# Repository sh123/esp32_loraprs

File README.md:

# ESP32 LoRa APRS Modem 

This project is amateur radio ESP32 based LoRa/FSK **KISS Bluetooth/BLE/USB/TCPIP** modem + LoRa **APRS-IS RX/TX iGate** server over WiFI + LoRa/FSK **APRS digipeater** + **Codec2 DV modem** (with Codec2 Talkie Android application). 

&#x26A0; **To configure sketch modify default parameters in config.h file or board specific pinouts in variants/[board]/variant.h.**

- For project description, detailed setup and more information, please, visit our Wiki at https://github.com/sh123/esp32_loraprs/wiki
- For discussions, visit https://github.com/sh123/esp32_loraprs/discussions

&#x26A0; Project also supports **APRSDroid TNC2 text APRS packet mode** (configurable), which makes it interoperable with other LoRa APRS trackers without AX25 support.

Supported module types: **SX126X**, **SX127X** and other modules supported by RadioLib, idle RX power consumption is around 60mA, so single 18650 cell should last for about 24 hours in RX.

Modules, which are used by users and known to work
- **SX126X** (**suggested**, 1W/2W modules will provide decent coverage for APRS, stable frequency suitable for < 125 kHz BW at 433 MHz, 5V from USB power bank is enough to power it, has additional LNA)
  - &#128077; **E22-400M30S/E22-400M33S (SX1268)**
  - E220-400M30S (LLCC68) BW125 SF from 7 to 9 (chip limitations)
  - These modules are 30dbm modules, but maximum power should be set to no more than 20-22dbm, see https://github.com/jgromes/RadioLib/wiki/High-power-Radio-Modules-Guide
- **SX127X** (low power, 50-100mW, temperature frequency drift, problematic for narrow band)
  - RA-01 (SX1278)
  - RA-02 (SX1276)
  - TTGO T-Beam (SX1276)

# Building
- Update `include/config.h` with your radio settings
  - If you are using lora-aprs iGate (non AX.25) then set `CFG_TEXT_PACKETS` and `CFG_TEXT_PACKETS_3` config parameters to `true` and use APRSDroid TNC2 connection protocol
- To build for client/tracker mode use `pio run -e esp32dev_e22_modem`
- To build for iGate mode use `pio run -e esp32dev_e22_igate`

# Development board
Development board schematics, case and antenna models are available under `extras/cad` and `extras/schematics`. 

Supported ESP32-DEV boards are with 36 and 38 pinouts (configured with solder pads) and ESP32-C3-MINI with separate dev board.

&#x26A0; **There are ESP32 boards with different socket widths: 22mm and 25mm, board files for 25mm have _wide suffix in file names.**

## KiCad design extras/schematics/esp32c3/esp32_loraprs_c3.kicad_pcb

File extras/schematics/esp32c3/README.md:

# ESP32-C3-MINI LoRa modem devboard

This is power bank style LoRA APRS modem based on ESP32-C3-DEV board with built in charge/boost IP5306 controller and battery holder on the back side.

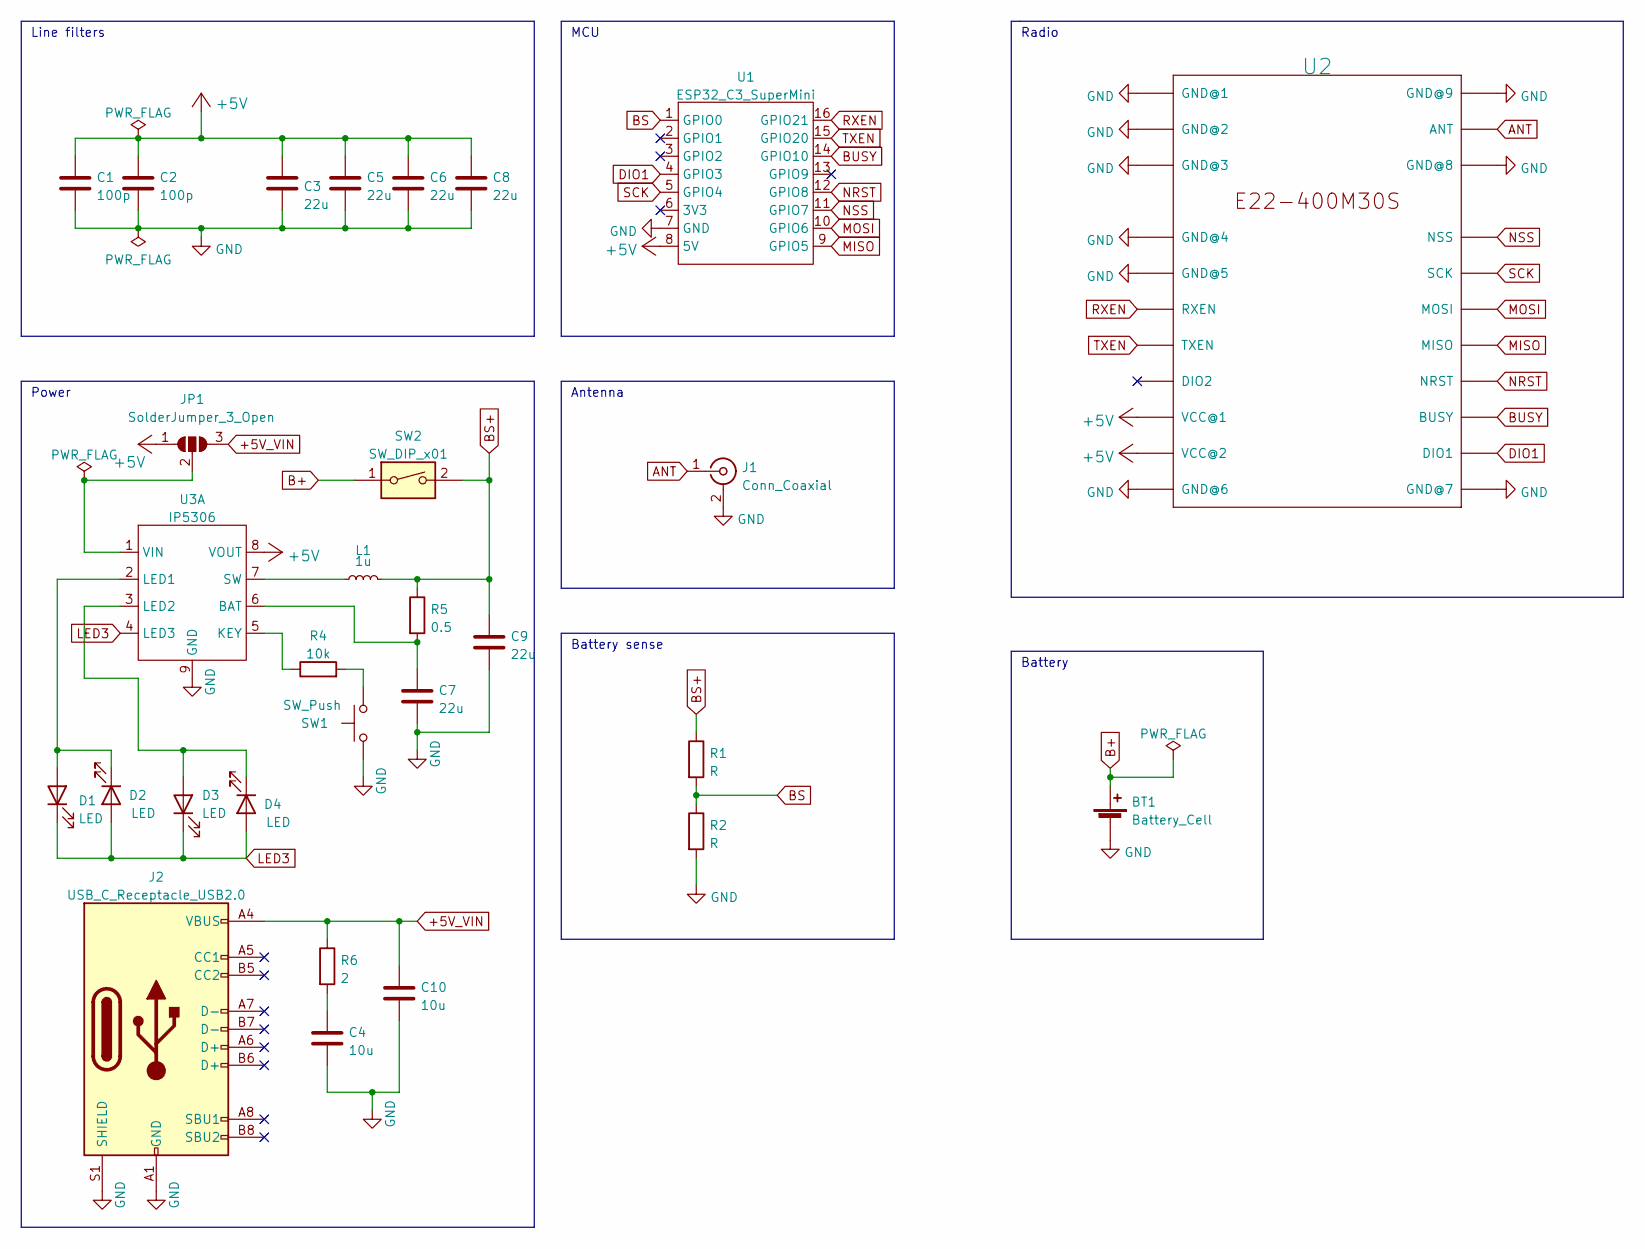
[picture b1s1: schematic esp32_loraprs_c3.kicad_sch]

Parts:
BT1: Battery_Cell; BatteryHolder_1x18650
C1, C2: 100p; C_0603_1608Metric_Pad1.08x0.95mm_HandSolder
C3, C5, C6, C7, C8, C9: 22u; C_0805_2012Metric_Pad1.18x1.45mm_HandSolder
C4, C10: 10u; C_0805_2012Metric_Pad1.18x1.45mm_HandSolder
D1, D2, D3, D4: LED; LED_0603_1608Metric_Pad1.05x0.95mm_HandSolder
J1: Conn_Coaxial; SMA_Samtec_SMA-J-P-X-ST-EM1_EdgeMount
J2: USB_C_Receptacle_USB2.0; USB_C_Receptacle_G-Switch_GT-USB-7010ASV
JP1: SolderJumper_3_Open; SolderJumper-3_P1.3mm_Open_RoundedPad1.0x1.5mm_NumberLabels
L1: 1u; L_6.3x6.3_H3
R1, R2: R; R_0603_1608Metric_Pad0.98x0.95mm_HandSolder
R4: 10k; R_0603_1608Metric_Pad0.98x0.95mm_HandSolder
R5: 0.5; R_0603_1608Metric_Pad0.98x0.95mm_HandSolder
R6: 2; R_0603_1608Metric_Pad0.98x0.95mm_HandSolder
SW1: SW_Push; Panasonic_EVQPUJ_EVQPUA
SW2: SW_DIP_x01; SW_SPST_REED_CT05-XXXX-J1
U1: ESP32_C3_SuperMini; esp32 c3 SuperMini
U2: E22-400M30S
U3: IP5306; HSOP-8-1EP_3.9x4.9mm_P1.27mm_EP2.3x2.3mm

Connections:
+5V: C1.1, C2.1, C3.1, C5.1, C6.1, C8.1, JP1.1 (A), U1.8 (5V), U2.9 (VCC@1), U2.10 (VCC@2), U3.8 (VOUT)
+5V_VIN: C10.1, J2.A4 (VBUS), J2.A9 (VBUS), J2.B4 (VBUS), J2.B9 (VBUS), JP1.3 (B), R6.1
ANT: J1.1 (In), U2.21 (ANT)
B+: BT1.1 (+), SW2.1
BS: R1.2, R2.1, U1.1 (GPIO0)
BS+: C9.1, L1.2, R1.1, R5.1, SW2.2
BUSY: U1.14 (GPIO10), U2.14 (BUSY)
DIO1: U1.4 (GPIO3), U2.13 (DIO1)
GND: BT1.2 (-), C1.2, C2.2, C3.2, C4.2, C5.2, C6.2, C7.2, C8.2, C9.2, C10.2, J1.2 (Ext), J2.A1 (GND), J2.A12 (GND), J2.B1 (GND), J2.B12 (GND), J2.S1 (SHIELD), R2.2, SW1.1, U1.7 (GND), U2.1 (GND@1), U2.2 (GND@2), U2.3 (GND@3), U2.4 (GND@4), U2.5 (GND@5), U2.11 (GND@6), U2.12 (GND@7), U2.20 (GND@8), U2.22 (GND@9), U3.9 (GND)
LED3: D1.1 (K), D2.2 (A), D3.1 (K), D4.2 (A), U3.4 (LED3)
MISO: U1.9 (GPIO5), U2.16 (MISO)
MOSI: U1.10 (GPIO6), U2.17 (MOSI)
NRST: U1.12 (GPIO8), U2.15 (NRST)
NSS: U1.11 (GPIO7), U2.19 (NSS)
unnamed: C4.1, R6.2
unnamed: C7.1, R5.2, U3.6 (BAT)
unnamed: D1.2 (A), D2.1 (K), U3.2 (LED1)
unnamed: D3.2 (A), D4.1 (K), U3.3 (LED2)
unnamed: JP1.2 (C), U3.1 (VIN)
unnamed: L1.1, U3.7 (SW)
unnamed: R4.1, U3.5 (KEY)
unnamed: R4.2, SW1.2
RXEN: U1.16 (GPIO21), U2.6 (RXEN)
SCK: U1.5 (GPIO4), U2.18 (SCK)
TXEN: U1.15 (GPIO20), U2.7 (TXEN)

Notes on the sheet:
Radio
MCU
Line filters
Battery sense
Power
Battery
Antenna

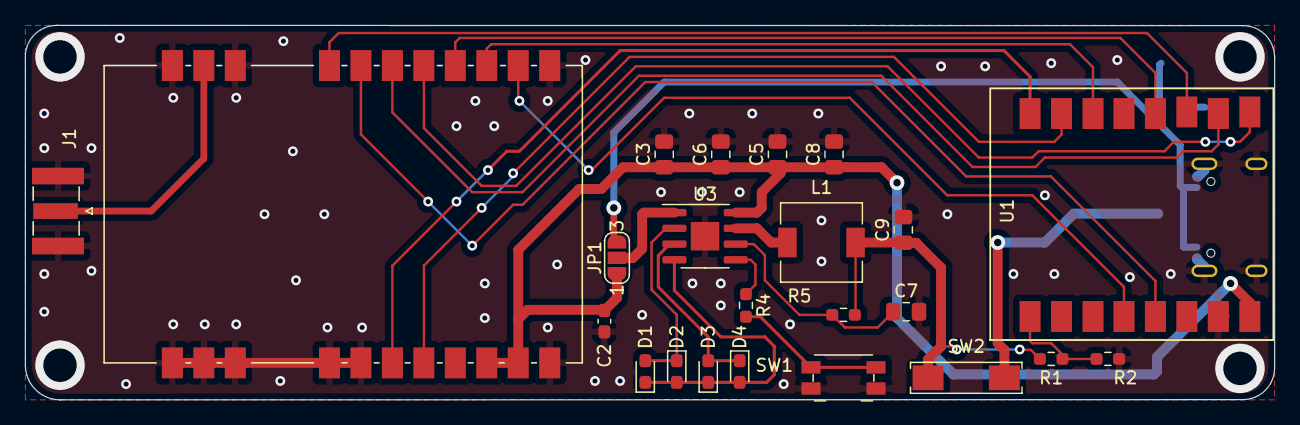
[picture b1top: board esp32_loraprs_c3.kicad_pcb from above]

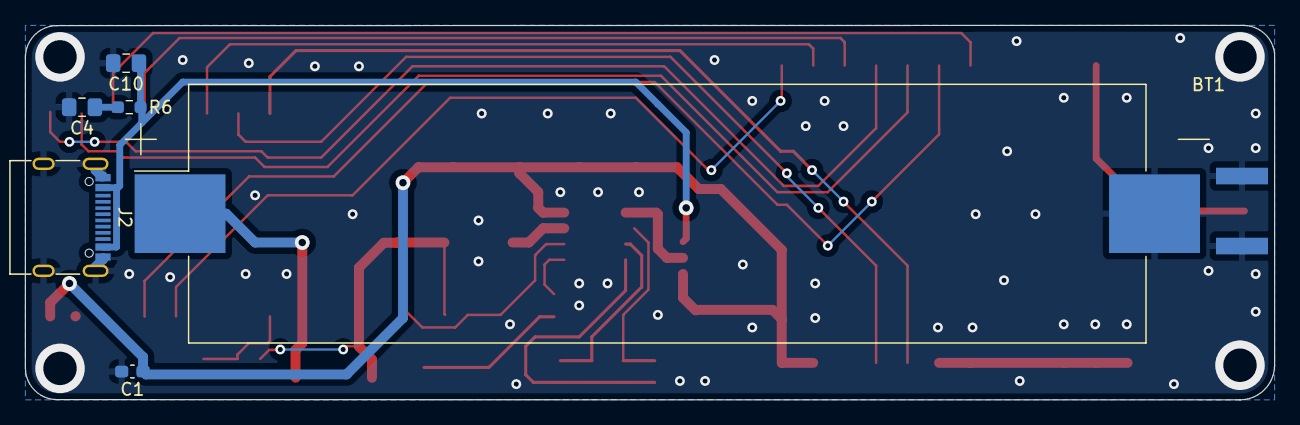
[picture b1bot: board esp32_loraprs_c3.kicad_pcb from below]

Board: 2 copper layers, 100.8 x 30.2 mm, 29 parts (6 on the bottom side), 25 nets.

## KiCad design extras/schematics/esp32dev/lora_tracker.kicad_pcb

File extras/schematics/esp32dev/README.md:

# ESP32 LoRa modem devboard

This is small universal ESP32 devkit LoRa prototyping board for RA-01 or E22-400M30S modules on the same board. 

Suitable for two different narrower ESP32 devkit board types with different pinouts (38 pins and 36 pins). 

Pinout configuration is done via solder pads.

&#x26A0; **There are ESP32 boards with different socket widths: 22mm and 25mm, board files for 25mm have _wide suffix in file names.**

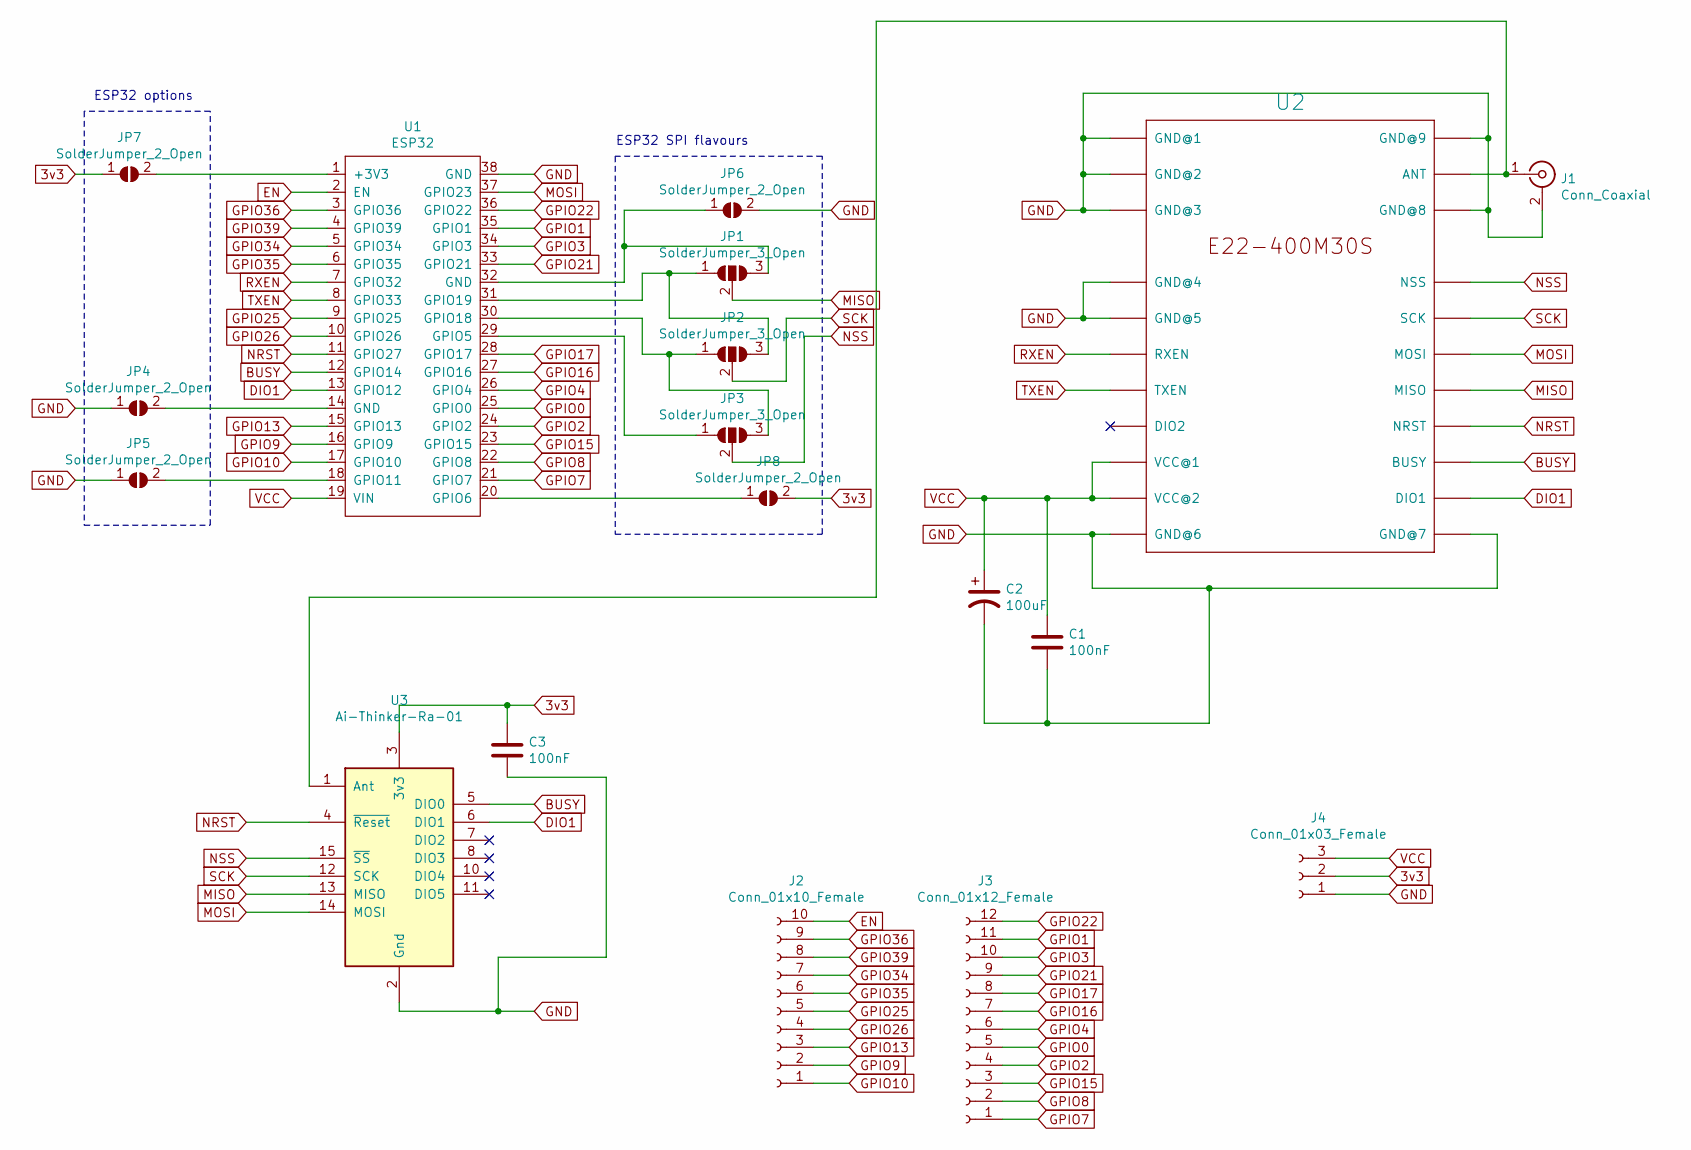
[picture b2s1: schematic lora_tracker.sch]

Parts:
C1, C3: 100nF; C_0603_1608Metric_Pad1.05x0.95mm_HandSolder
C2: 100uF; CP_Elec_3x5.3
J1: Conn_Coaxial; SMA_Samtec_SMA-J-P-H-ST-EM1_EdgeMount
J2: Conn_01x10_Female; PinSocket_1x10_P2.54mm_Vertical
J3: Conn_01x12_Female; PinSocket_1x12_P2.54mm_Vertical
J4: Conn_01x03_Female; PinSocket_1x03_P2.54mm_Vertical
JP1, JP2, JP3: SolderJumper_3_Open; SolderJumper-3_P1.3mm_Open_Pad1.0x1.5mm
JP4, JP5, JP6, JP7, JP8: SolderJumper_2_Open; SolderJumper-2_P1.3mm_Open_Pad1.0x1.5mm
U1: ESP32; esp32-devkit-wide
U2: E22-400M30S
U3: Ai-Thinker-Ra-01; Ai-Thinker-Ra-01-LoRa

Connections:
3v3: C3.1, J4.2, JP7.1 (A), JP8.2 (B), U3.3 (3v3)
BUSY: U1.12 (GPIO14), U2.14 (BUSY), U3.5 (DIO0)
DIO1: U1.13 (GPIO12), U2.13 (DIO1), U3.6 (DIO1)
EN: J2.10, U1.2 (EN)
GND: C1.2, C2.2, C3.2, J1.2 (Ext), J4.1, JP4.1 (A), JP5.1 (A), JP6.2 (B), U1.38 (GND), U2.1 (GND@1), U2.2 (GND@2), U2.3 (GND@3), U2.4 (GND@4), U2.5 (GND@5), U2.11 (GND@6), U2.12 (GND@7), U2.20 (GND@8), U2.22 (GND@9), U3.2 (Gnd), U3.9 (Gnd), U3.16 (Gnd)
GPIO0: J3.5, U1.25 (GPIO0)
GPIO1: J3.11, U1.35 (GPIO1)
GPIO2: J3.4, U1.24 (GPIO2)
GPIO3: J3.10, U1.34 (GPIO3)
GPIO4: J3.6, U1.26 (GPIO4)
GPIO7: J3.1, U1.21 (GPIO7)
GPIO8: J3.2, U1.22 (GPIO8)
GPIO9: J2.2, U1.16 (GPIO9)
GPIO10: J2.1, U1.17 (GPIO10)
GPIO13: J2.3, U1.15 (GPIO13)
GPIO15: J3.3, U1.23 (GPIO15)
GPIO16: J3.7, U1.27 (GPIO16)
GPIO17: J3.8, U1.28 (GPIO17)
GPIO21: J3.9, U1.33 (GPIO21)
GPIO22: J3.12, U1.36 (GPIO22)
GPIO25: J2.5, U1.9 (GPIO25)
GPIO26: J2.4, U1.10 (GPIO26)
GPIO34: J2.7, U1.5 (GPIO34)
GPIO35: J2.6, U1.6 (GPIO35)
GPIO36: J2.9, U1.3 (GPIO36)
GPIO39: J2.8, U1.4 (GPIO39)
MISO: JP1.2 (C), U2.16 (MISO), U3.13 (MISO)
MOSI: U1.37 (GPIO23), U2.17 (MOSI), U3.14 (MOSI)
NRST: U1.11 (GPIO27), U2.15 (NRST), U3.4 (~Reset)
NSS: JP3.2 (C), U2.19 (NSS), U3.15 (~SS)
unnamed: J1.1 (In), U2.21 (ANT), U3.1 (Ant)
unnamed: JP1.1 (A), JP2.3 (B), U1.31 (GPIO19)
unnamed: JP1.3 (B), JP6.1 (A), U1.32 (GND)
unnamed: JP2.1 (A), JP3.3 (B), U1.30 (GPIO18)
unnamed: JP3.1 (A), U1.29 (GPIO5)
unnamed: JP4.2 (B), U1.14 (GND)
unnamed: JP5.2 (B), U1.18 (GPIO11)
unnamed: JP7.2 (B), U1.1 (+3V3)
unnamed: JP8.1 (A), U1.20 (GPIO6)
RXEN: U1.7 (GPIO32), U2.6 (RXEN)
SCK: JP2.2 (C), U2.18 (SCK), U3.12 (SCK)
TXEN: U1.8 (GPIO33), U2.7 (TXEN)
VCC: C1.1, C2.1, J4.3, U1.19 (VIN), U2.9 (VCC@1), U2.10 (VCC@2)

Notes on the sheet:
ESP32 SPI flavours
ESP32 options

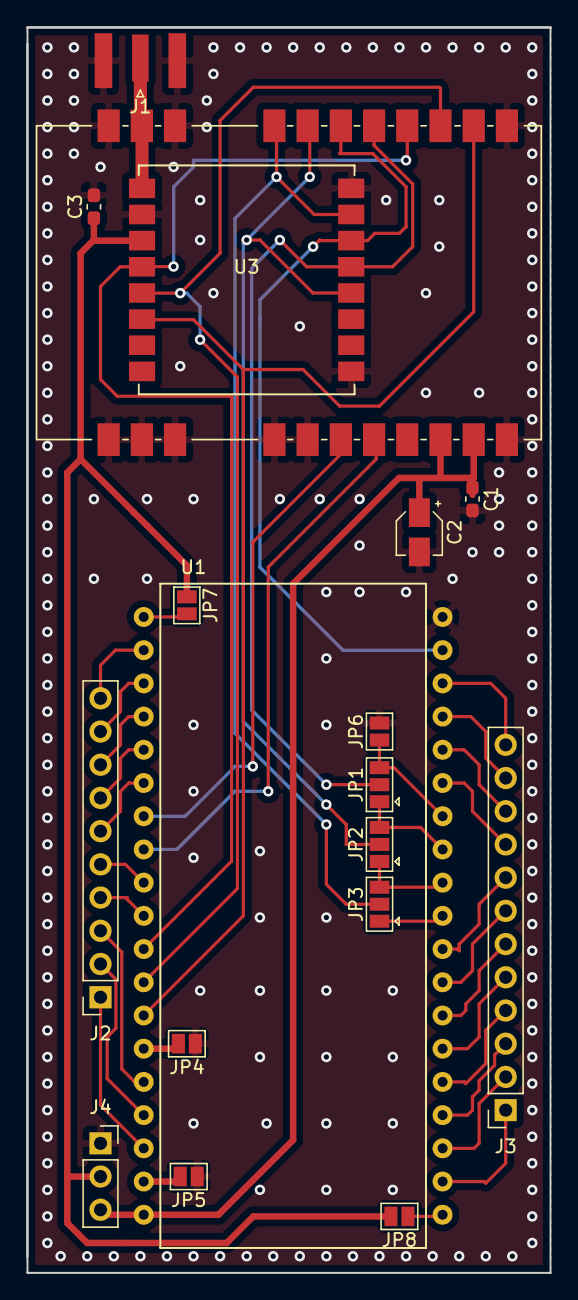
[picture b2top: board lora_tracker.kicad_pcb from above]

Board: 2 copper layers, 40.0 x 95.2 mm, 18 parts (0 on the bottom side), 43 nets.

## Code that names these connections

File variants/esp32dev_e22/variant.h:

#ifndef VARIANT_H
#define VARIANT_H

// module name
#define USE_SX126X
#define MODULE_NAME           SX1268    // 433 MHz modules

// lora pinouts
#define CFG_LORA_PIN_NSS      5
#define CFG_LORA_PIN_RST      27    // could be also 26 on early boards, check schematics
#define CFG_LORA_PIN_DIO1     12    // (sx127x - dio0, sx126x/sx128x - dio1)
#define CFG_LORA_PIN_BUSY     14    // (sx127x - dio1, sx126x/sx128x - busy)
#define CFG_LORA_PIN_RXEN     32    // (sx127x - unused, sx126x - RXEN pin number)
#define CFG_LORA_PIN_TXEN     33    // (sx127x - unused, sx126x - TXEN pin number)

// built in led
#define BUILTIN_LED           2     // heartbeat led

// Enable modem telemetry
#define CFG_TLM_BAT_MON_CAL   0.37f   // voltage correction
#define CFG_TLM_BAT_MON_PIN   36      // battery ADC pin

#endif // VARIANT_H

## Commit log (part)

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2021-06-08 Simplify repeated code
2021-06-08 Use more consistent name
2021-10-15 Set implicit header mode for spreading factor of 6
2021-10-16 Set implicit header mode for sf = 6
2021-10-16 Added support for radiolib through #ifdef
2021-10-16 Print errors
2021-10-16 Fixes for receive
2021-10-16 Fixes
2021-10-17 Ongoing fixes
2021-10-18 Code cleanup
2021-10-20 Fix frquency setting, use static buffer
2021-10-20 Implemented restart command
2021-10-20 Added log line
2021-10-20 Better selection between radiolib and arduino-lora
2021-10-20 Comment
2021-10-20 Radiolib support (#23)
    - Radiolib support
2021-10-20 Configuraion improvements
2021-10-20 Added image
2021-10-20 Update image
2021-10-20 Added images
2021-10-20 Added RadioLib based carrier detect
2021-10-21 Add options to enable kiss over tcp/ip and AP mode
2021-10-21 Needs wifi when KissEnableTcpIp is true
2021-10-21 Use wifi when KISS TCP/IP is needed
2021-10-21 Bug fixes
2021-10-21 Added support for soft ap
2021-10-21 WiFi AP does not require re-connection
2021-10-21 Disable APRS-IS when WiFi is in AP mode
2021-10-21 Small refactoring
2021-10-21 Bug fixing
2021-10-21 Documentation
2021-10-21 KISS TCP/IP server fixes
2021-10-21 Drop previous client if new one is connecting
2021-10-21 Update documenation
2021-10-21 Improve log lines
2021-10-22 Use debug log facility
2021-10-22 Usb serial support
2021-10-22 Tuning
2021-10-22 Set USE_RADIOLIB by default
2021-10-22 Disable logging when USB is enabled
2021-10-22 Improve logging
2021-10-22 Add support for USB-OTG operation and improve logging (#25)
    * Use debug log facility
    * Usb serial support
    * Tuning
    * Disable logging when USB is enabled
    * Improve logging
    * Improve logging
2021-10-22 Disable bluetooth if USB mode is active
2021-10-23 Update diagram
2021-10-23 Added yED diagram
2021-10-23 Add csma diagram
2021-10-23 Add image
2021-10-25 Take module name from file
2021-10-25 Cleanup
2021-10-25 Rename module.h to module_name.h
2021-10-26 Add configuration flag to allow text aprs messaging
2021-10-26 Add ability to disable KISS and run in TNC2 mode
2021-10-26 Update doc string
2021-10-26 Fixes for TNC2 support
2021-10-26 Comments, logging
2021-10-26 Improve and refactor
2021-10-26 Append \0 in receive
2021-10-26 Logging
2021-10-26 Remove some magic constants
2021-10-28 Uses SX1268
    fix three SX1268 unimplemented functions in RadioLib
2021-10-30 Update comment
2021-10-31 Pass Dio1 pin to module
2021-10-31 Rename dio0/dio1 to A/B to make them more generic
2021-10-31 Update doc strings
2021-11-10 Uses SX1268 (#28)
    fix three SX1268 unimplemented functions in RadioLib
2021-11-10 Set default module to SX1278
2021-11-12 Fix compilation issue when using lora lib
2021-11-12 Add config option to set debug level, add trace calls for incoming and outgoing data
2021-11-12 Add configurable support for reading in ISR vs reading on separate task
2021-11-13 Fix wrong define usage
2021-11-13 Fix bug with log levels
2021-11-13 Improve module selection
2021-11-13 Additional module type logging
2021-11-13 Additional logging
2021-11-15 Added doc image
2021-11-15 Move RF switch pin selection to config, allow to specify all options in config.h
2021-11-20 Use current rx status is CAD for sx126x
2021-11-20 Improve logic
2021-11-22 Allow specifying some more lora parameters from config.h
2021-11-22 Doc string
2021-11-22 Log minimum decode level
2021-11-22 B pin must be set for sx126x
2021-11-22 Change default sync world to 0x12
2021-11-23 Small config update
2021-11-23 Include frequency error into the comment only when it is not 0
2021-11-23 Replace MODULE_NAME == with USE_SX126X
2022-02-03 Added schematics and cad models
2022-02-03 Added readme
2022-03-11 Add support for split operation
2022-06-18 Set scan response and min/max preffered intervals
2022-06-19 Additional ble logging
2022-06-19 Update log lines
2022-06-20 Performance optimizations
2022-06-20 Logging update
2022-06-21 Added time on air logging
2022-06-21 Time on air logging
2022-07-06 Include signal report into the aprs position packet with messaging support
2022-07-06 Signal report for mic-e packets
2022-08-25 Inject filter out proprietary identifier used by another tracker to make it interoperable
2022-08-25 Move proprietary identifier filtering higher
2022-08-25 Cosmetic fix
2022-08-26 Fix bug with overriding last char in info
2022-09-05 Update ERR_NONE -> RADIOLIB_ERR_NONE for new radiolib
2022-09-21 Added gerber files
2022-10-16 Fix CRC enabling for loralib
2022-10-16 Fix issue with wrong path being digirepeated
2022-10-16 Use xTaskNotifyFromISR/xTaskNotifyWait to notify on incoming data from ISR
2022-12-01 Add * suffix for digirepaters only
2022-12-03 Remove loralib dependency
2022-12-03 Refactor task
2022-12-03 Refactoring
2022-12-03 Remove dependency on arduino-LoRa library, use RadioLib only (#42)
    - Remove dependency on arduino-LoRa library, use RadioLib only
    - Run radio TX on the same task where RX is running
    - Refactor for better readability
2022-12-03 Minor refactoring
2022-12-03 Renames
2022-12-03 Increase version
2022-12-03 Trace logging
2022-12-10 Do not clear dio action if it is not set
2022-12-11 Update rig to serial queue logic
2022-12-11 Use lora-aprs 3 byte prefix only if specified in config
2022-12-11 Comments
2022-12-11 More interoperability cases
2022-12-11 Do not drop prefix in received
2022-12-11 Images
2022-12-11 Revert previous change
2022-12-12 Remove 4 byte prefix
2022-12-13 Send lora-aprs prefix in ordinary transmission
2022-12-14 Update default pinouts
2022-12-14 Formatting
2022-12-17 Add option to monitor battery level
2022-12-18 Moved to platformio
2022-12-18 Moved cad models and schematics under extras
2022-12-18 Added .gitignore
2022-12-18 Specify upload protocol
2022-12-18 Refactor platformio.ini
2022-12-18 Allow building igate mode from platformio file
2022-12-18 Move images to extras
2022-12-19 Use specific arduinoespressif version
2022-12-19 Added ttgo-lora32-v1
2022-12-19 Rename file and update gitignore
2022-12-19 Fix warnings
2022-12-19 Do not send telemetry in igate mode and send battery level every minute
2022-12-19 Switch project from Arduino to PlatformIO (#52)
    * Moved to platformio
    * Moved cad models and schematics under extras
    * Update README.md
    * Added .gitignore
    * Specify upload protocol
    * Refactor platformio.ini
2022-12-19 Added more cad models
2022-12-19 Added more models
2022-12-19 Added missing lib from schematics
2022-12-19 Removed old file
2022-12-19 Code styling
2022-12-19 Styling
2022-12-20 Split operation fixes
2022-12-20 Minor improvements
2022-12-20 Fix naming
2022-12-22 Improve half duplex operation
2022-12-22 Version logging
2022-12-30 Fix for TNC2 digi repeating
2023-01-03 Add fix for last character loss
2023-01-04 Allow digirepeating in client mode
2023-01-05 Fix typo
2023-03-15 Allow to specify preamble length and select modem type from platformio ini
2023-03-15 Update espressif and libraries to latest versions
2023-03-18 Fix lib table
2023-03-18 Added wide board pcb
2023-08-09 Added lora32-v2 env
2023-11-12 Updated Espressif and libraries to latest version
2023-11-16 Add support for FSK modulation
2023-11-17 Avoid switching to rx on each packet
2023-11-17 Handle control data escape
2023-11-17 Update SetHardware command
2023-11-17 Convert to khz
2023-11-17 Serial tx delay update
2023-12-01 Fix issue with RadioLib API changes
2024-10-30 Updated schematics project
2024-11-03 Add missing files
2024-11-26 Heltec_wifi_lora_32_V3 Support. Compiled. To be tested
2024-11-28 Corrected MODULE NAME
2025-04-11 Documentation, small refactoring
2025-04-24 Fixed bux #1 and other stuff to make it works (tested on 2 heltec wireless stick lite v3)
2025-08-29 Heltec V3 BLE build fixes: deps, pins, SX1262, timer, logging shim
2025-12-16 Added schematics
2025-12-16 Update README with ESP32-C3 and board width details
    Added information about ESP32-C3 support and board widths.
2025-12-17 Modularized board variants
2025-12-17 Dep update
2025-12-17 Upgrade libraries
2025-12-17 Update pinouts
2025-12-17 BLE optimizations
2025-12-18 Added separate version file
2025-12-18 Fixed warnings
2025-12-19 Update README with RX power consumption details
    Added information about idle RX power consumption and battery life.
2025-12-20 Refactor
2025-12-30 esp32c3 tuneup
2025-12-30 Update schematics
2025-12-30 Updated variant
2025-12-30 Tunning debug/release
2025-12-30 Added DIP switch for battery
2025-12-30 Increased version
2025-12-30 Correct board name and charge controller in README
    Updated the README to reflect the correct board name and charge controller details.
2026-01-01 Additional files to extras
2026-01-01 Update frequency
2026-01-02 Restructure cad directory
2026-01-02 Config
2026-01-02 Added model
2026-01-02 Update model
2026-01-03 Updated models
2026-01-08 Rewrite ble_serial to use nimble and circual buffer
2026-01-09 Refactor configs
2026-01-09 Implement BLESerial::end
2026-01-09 BLE pin auth
2026-01-09 Reformat code
2026-01-09 Proper pass key handling
2026-01-09 Update ini file
2026-01-09 Remove unused variable
2026-01-10 Update voltage correction for esp32c3 board
2026-01-11 Refactor config logic and add raw repeater
2026-01-11 Cosmetic changes
2026-01-11 Use BLE on esp32dev by default but provide option for bt classic
2026-01-11 Refactor settings
2026-01-11 Refactor config
2026-01-11 Added repeater platformio.ini entry
2026-01-11 Added split repeater configuration
2026-01-12 Update models
2026-01-19 Update platformio.ini
    changed environment to the correct ra01 modem for bluetooth
2026-01-19 Update platformio.ini (#78)
    changed environment to the correct ra01 modem for bluetooth
2026-01-26 Small fix
2026-01-30 Update variant files
2026-01-31 esp32c3 cad fixes
2026-01-31 Added button
2026-02-02 Added sx1262 variant files
2026-02-02 Added more variants
2026-02-03 Added better lid models with hook
2026-02-04 Update lid model
2026-02-24 Variant file updates
2026-02-24 Added experimental meshtastic variant files
2026-02-25 Set lora parameters for meshcore repeater
2026-02-25 Added pins_arduino.h
2026-02-25 Use ACM ports for c3
2026-02-28 Experimenting with meshtastic
2026-03-30 Added partition file
2026-03-30 Fix formatting of code snippet in README.md
2026-03-30 Add build flags for MAX_CONTACTS and MAX_GROUP_CHANNELS
